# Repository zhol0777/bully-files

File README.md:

# bully-files

Bully is a keyboard designed by paaradiso keyboard design and zhol. It combines low typing angle, a plateless build, and modest but dignified design sensibilities. Its 13.5u width layout is designed for maximum compatibility with base kits that are missing minimum 40% keyboard support (“3-key”). Bully has a 22.4mm EKH, 4.0 degree angle, and bezels measuring 8mm and 3mm. 

The case files are provided in the [./case](./case/) directory, and alternative tops for HHKB layout (1.25u blocker) and WKL (1.25u blocker) are provided in their respective directories. 

This ran in a private run and public run by Coffee Break Keyboards in Q1 2023 and fulfilling Q2 2023.

## Required components
* Daughterboard
  * It is designed for [C3 Unified Daughterboard](https://github.com/Unified-Daughterboard/UDB-C-Legacy), but an updated daughterboard that takes JST-SH cables is provided [here](https://github.com/Unified-Daughterboard/UDB-C-JSH).
* Tadpoles
  * bully's PCB is fit into the case not with screws, but 8 injection molded rubber inserts named "tadpoles", from Geonworks.
  * [Files, courtesy Geon](https://geon.works/pages/tadpole-files)
* Screws
  * All screws are M2. Screws for daughterboard are 4mm, case screws are 6-ish mm.
* JST cable
  * As sold, bully took a 50mm 4-pin JST-SH cable. These cables are wired 1:1. I had no issues with Adafruit Qwiic JST SH cables sourced from Mouser. If you use an alternative connector on your PCB and daughterboard, you will need to ensure those cables are also 1:1.
* PCB
  * PCB edge cuts and plate files are provided in the [./misc](./misc/) directory. An electro-capacitive (commonly known as Topre, or NIZ Plum) compatible PCB is provided by sporkus [here](https://github.com/sporkus/capybully_keyboard). An alternative PCB compatible with Cherry MX and Alps switches is provided by sporkus [here](https://github.com/sporkus/bully2040_keyboard).
* Case feet.
  * bully uses [SKUF feet](https://github.com/Zambumon/SKUF).

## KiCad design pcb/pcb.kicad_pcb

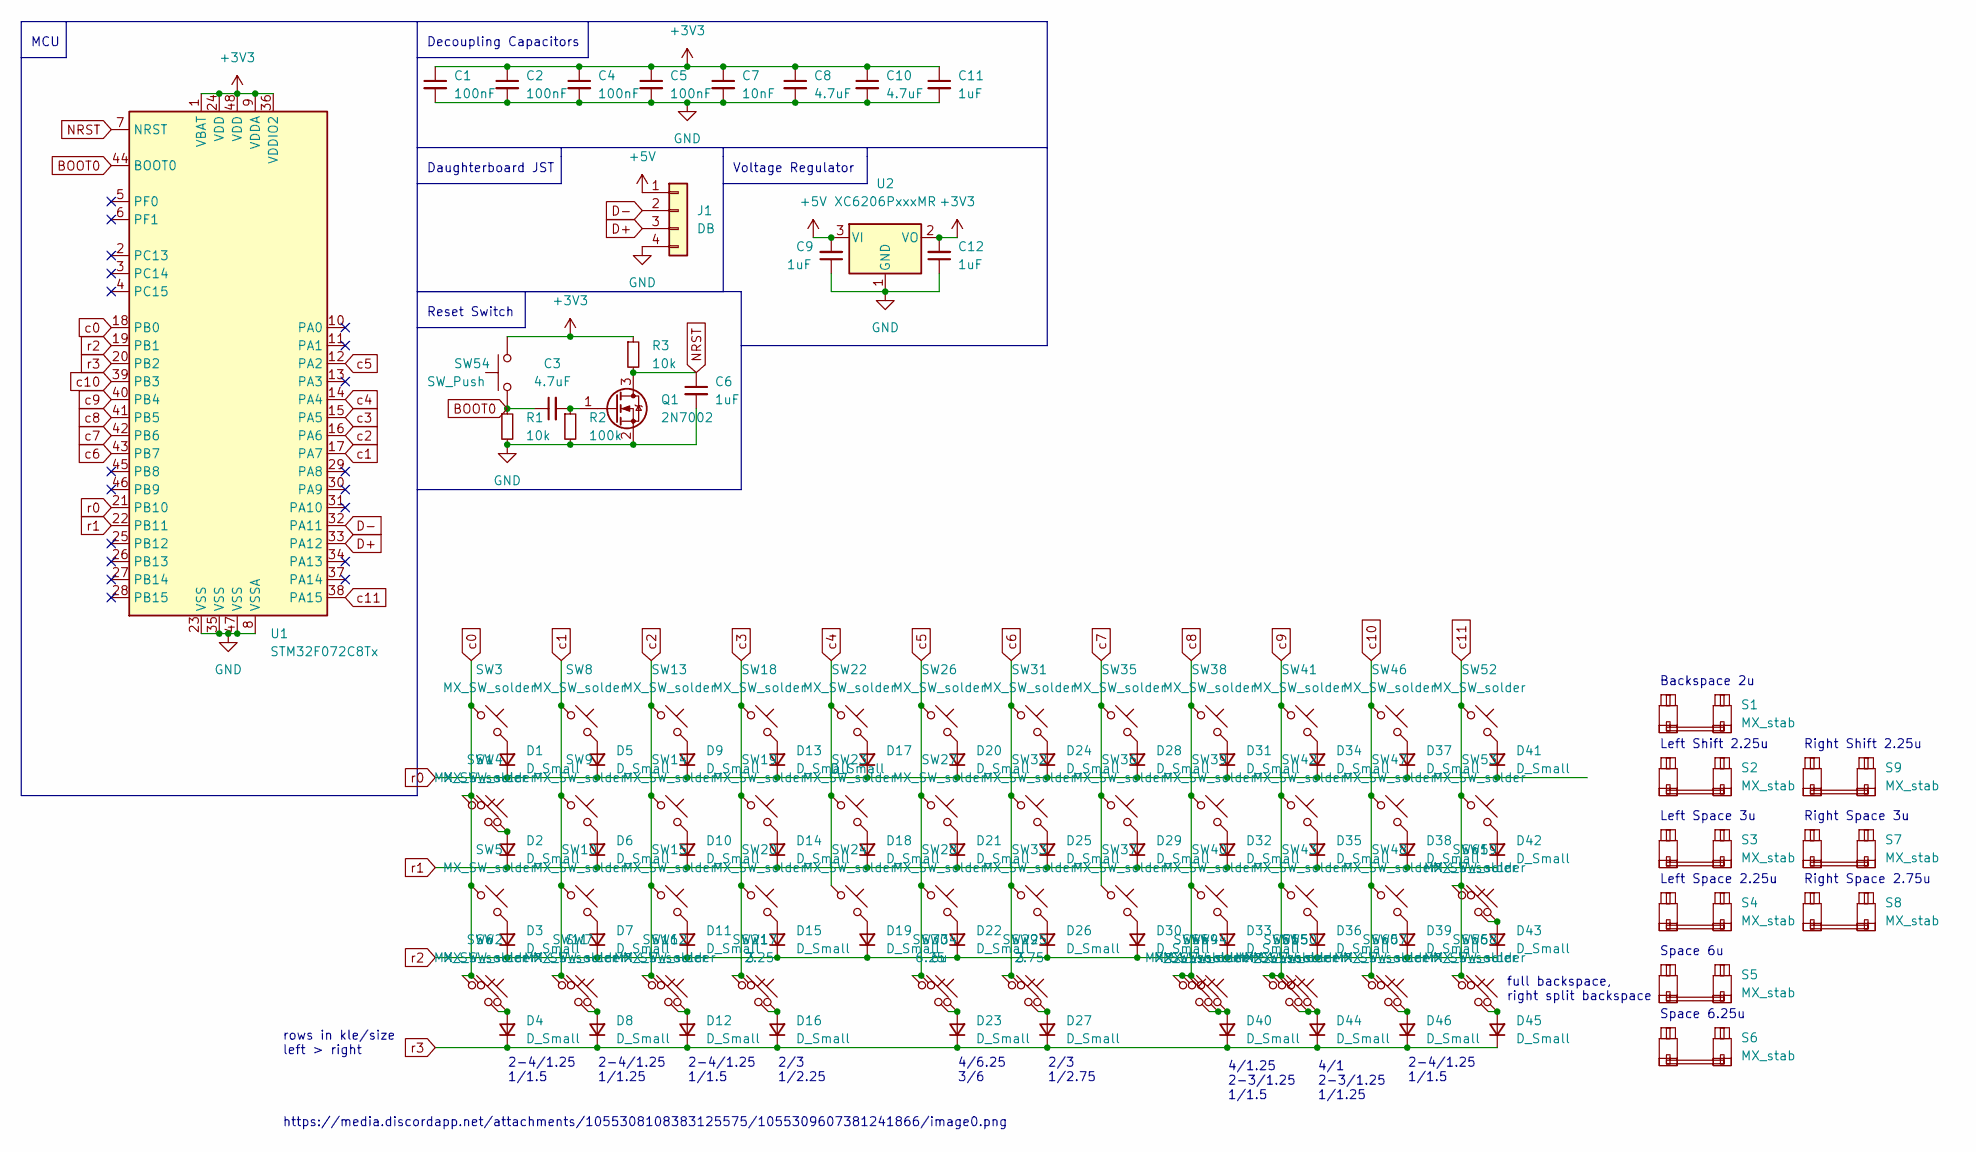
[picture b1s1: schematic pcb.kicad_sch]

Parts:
C1, C2, C4, C5: 100nF; C_0402_1005Metric
C3, C8, C10: 4.7uF; C_0402_1005Metric
C6, C9, C11, C12: 1uF; C_0402_1005Metric
C7: 10nF; C_0402_1005Metric
D1, D2, D3, D4, D5, D6, D7, D8, D9, D10, D11, D12, D13, D14, D15, D16, D17, D18, D19, D20, D21, D22, D23, D24, D25, D26, D27, D28, D29, D30, D31, D32, D33, D34, D35, D36, D37, D38, D39, D40, D41, D42, D43, D44, D45, D46: D_Small; D_SOD-123
J1: DB; JST_SH_SM04B-SRSS-TB_1x04-1MP_P1.00mm_Horizontal
Q1: 2N7002; SOT-23
R1, R3: 10k; R_0402_1005Metric
R2: 100k; R_0402_1005Metric
S1: MX_stab; STAB_MX_P_2u
S2, S4, S9: MX_stab; STAB_MX_P_2.25u
S3, S7: MX_stab; STAB_MX_P_3u
S5: MX_stab; STAB_MX_6u
S6: MX_stab; STAB_MX_6.25u
S8: MX_stab; STAB_MX_P_2.75u
SW1, SW53: MX_SW_solder; SW_MX_1.75u
SW2, SW3, SW12, SW44, SW57: MX_SW_solder; SW_MX_1.5u
SW4: MX_SW_solder; SW_MX_1.75u_stp
SW5, SW8, SW9, SW10, SW13, SW14, SW15, SW18, SW19, SW20, SW22, SW23, SW24, SW26, SW27, SW28, SW31, SW32, SW33, SW35, SW36, SW37, SW38, SW39, SW40, SW41, SW42, SW43, SW46, SW47, SW48, SW51, SW52, SW56, SW58, SW61: MX_SW_solder; SW_MX_1u
SW6, SW7, SW11, SW16, SW45, SW49, SW50, SW55, SW59, SW60: MX_SW_solder; SW_MX_1.25u
SW17: 2.25; SW_MX_1u
SW21, SW29: 3; SW_MX_1u
SW25: 2.75; SW_MX_1u
SW30: 6.25; SW_MX_1u
SW34: 6u; SW_MX_1u
SW54: SW_Push; SW_SPST_TL3342
U1: STM32F072C8Tx; LQFP-48_7x7mm_P0.5mm
U2: XC6206PxxxMR; SOT-23

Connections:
+3V3: C1.1, C2.1, C4.1, C5.1, C7.1, C8.1, C10.1, C11.1, C12.2, R3.1, SW54.2, U1.1 (VBAT), U1.9 (VDDA), U1.24 (VDD), U1.36 (VDDIO2), U1.48 (VDD), U2.2 (VO)
+5V: C9.2, J1.1, U2.3 (VI)
BOOT0: C3.1, R1.1, SW54.1, U1.44 (BOOT0)
D+: J1.3, U1.33 (PA12)
D-: J1.2, U1.32 (PA11)
GND: C1.2, C2.2, C4.2, C5.2, C6.2, C7.2, C8.2, C9.1, C10.2, C11.2, C12.1, J1.4, Q1.2 (S), R1.2, R2.2, U1.8 (VSSA), U1.23 (VSS), U1.35 (VSS), U1.47 (VSS), U2.1 (GND)
NRST: C6.1, Q1.3 (D), R3.2, U1.7 (NRST)
unnamed: D1.2 (A), SW3.2
unnamed: D2.2 (A), SW1.2, SW4.2
unnamed: D3.2 (A), SW5.2
unnamed: D4.2 (A), SW2.2, SW6.2
unnamed: D5.2 (A), SW8.2
unnamed: D6.2 (A), SW9.2
unnamed: D7.2 (A), SW10.2
unnamed: D8.2 (A), SW7.2, SW11.2
unnamed: D9.2 (A), SW13.2
unnamed: D10.2 (A), SW14.2
unnamed: D11.2 (A), SW15.2
unnamed: D12.2 (A), SW12.2, SW16.2
unnamed: D13.2 (A), SW18.2
unnamed: D14.2 (A), SW19.2
unnamed: D15.2 (A), SW20.2
unnamed: D16.2 (A), SW17.2, SW21.2
unnamed: D17.2 (A), SW22.2
unnamed: D18.2 (A), SW23.2
unnamed: D19.2 (A), SW24.2
unnamed: D20.2 (A), SW26.2
unnamed: D21.2 (A), SW27.2
unnamed: D22.2 (A), SW28.2
unnamed: D23.2 (A), SW30.2, SW34.2
unnamed: D24.2 (A), SW31.2
unnamed: D25.2 (A), SW32.2
unnamed: D26.2 (A), SW33.2
unnamed: D27.2 (A), SW25.2, SW29.2
unnamed: D28.2 (A), SW35.2
unnamed: D29.2 (A), SW36.2
unnamed: D30.2 (A), SW37.2
unnamed: D31.2 (A), SW38.2
unnamed: D32.2 (A), SW39.2
unnamed: D33.2 (A), SW40.2
unnamed: D34.2 (A), SW41.2
unnamed: D35.2 (A), SW42.2
unnamed: D36.2 (A), SW43.2
unnamed: D37.2 (A), SW46.2
unnamed: D38.2 (A), SW47.2
unnamed: D39.2 (A), SW48.2
unnamed: D40.2 (A), SW44.2, SW45.2, SW49.2
unnamed: D41.2 (A), SW52.2
unnamed: D42.2 (A), SW53.2
unnamed: D43.2 (A), SW59.2, SW61.2
unnamed: D44.2 (A), SW50.2, SW51.2, SW55.2
unnamed: D45.2 (A), SW56.2, SW58.2
unnamed: D46.2 (A), SW57.2, SW60.2
unnamed: C3.2, Q1.1 (G), R2.1
c0: SW1.1, SW2.1, SW3.1, SW4.1, SW5.1, SW6.1, U1.18 (PB0)
c1: SW7.1, SW8.1, SW9.1, SW10.1, SW11.1, U1.17 (PA7)
c2: SW12.1, SW13.1, SW14.1, SW15.1, SW16.1, U1.16 (PA6)
c3: SW17.1, SW18.1, SW19.1, SW20.1, SW21.1, U1.15 (PA5)
c4: SW22.1, SW23.1, SW24.1, U1.14 (PA4)
c5: SW26.1, SW27.1, SW28.1, SW30.1, SW34.1, U1.12 (PA2)
c6: SW25.1, SW29.1, SW31.1, SW32.1, SW33.1, U1.43 (PB7)
c7: SW35.1, SW36.1, SW37.1, U1.42 (PB6)
c8: SW38.1, SW39.1, SW40.1, SW44.1, SW45.1, SW49.1, U1.41 (PB5)
c9: SW41.1, SW42.1, SW43.1, SW50.1, SW51.1, SW55.1, U1.40 (PB4)
c10: SW46.1, SW47.1, SW48.1, SW57.1, SW60.1, U1.39 (PB3)
c11: SW52.1, SW53.1, SW56.1, SW58.1, SW59.1, SW61.1, U1.38 (PA15)
r0: D1.1 (K), D5.1 (K), D9.1 (K), D13.1 (K), D17.1 (K), D20.1 (K), D24.1 (K), D28.1 (K), D31.1 (K), D34.1 (K), D37.1 (K), D41.1 (K), U1.21 (PB10)
r1: D2.1 (K), D6.1 (K), D10.1 (K), D14.1 (K), D18.1 (K), D21.1 (K), D25.1 (K), D29.1 (K), D32.1 (K), D35.1 (K), D38.1 (K), D42.1 (K), U1.22 (PB11)
r2: D3.1 (K), D7.1 (K), D11.1 (K), D15.1 (K), D19.1 (K), D22.1 (K), D26.1 (K), D30.1 (K), D33.1 (K), D36.1 (K), D39.1 (K), D43.1 (K), U1.19 (PB1)
r3: D4.1 (K), D8.1 (K), D12.1 (K), D16.1 (K), D23.1 (K), D27.1 (K), D40.1 (K), D44.1 (K), D45.1 (K), D46.1 (K), U1.20 (PB2)

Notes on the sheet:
Backspace 2u
https://media.discordapp.net/attachments/1055308108383125575/1055309607381241866/image0.png
2-4/1.25 1/1.5
Daughterboard JST
Left Space 3u
4/1.25 2-3/1.25 1/1.5
full backspace, right split backspace
Voltage Regulator
2-4/1.25 1/1.25
Decoupling Capacitors
Right Shift 2.25u
2/3 1/2.75
rows in kle/size left > right
Right Space 3u
Space 6.25u
2/3 1/2.25
Reset Switch
4/1 2-3/1.25 1/1.25
Space 6u
Left Shift 2.25u
4/6.25 3/6
Right Space 2.75u
MCU
Left Space 2.25u

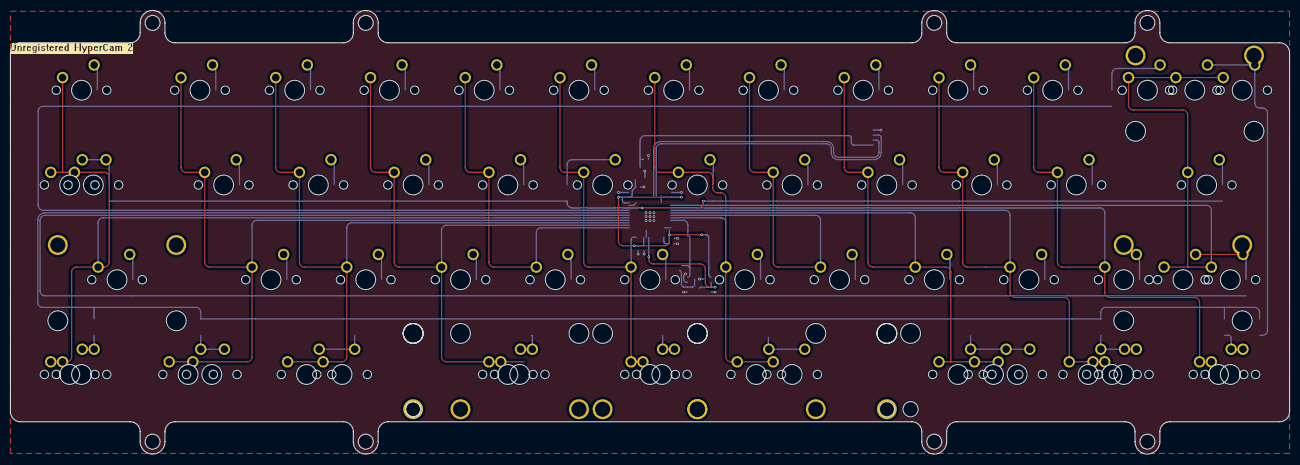
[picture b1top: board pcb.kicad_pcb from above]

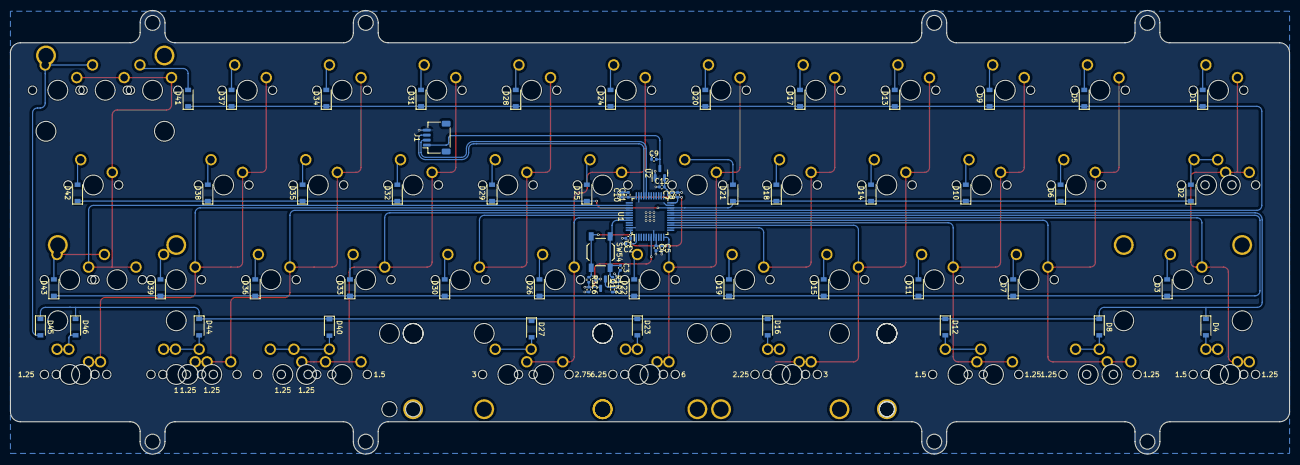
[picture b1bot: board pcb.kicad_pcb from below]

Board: 2 copper layers, 257.2 x 89.2 mm, 135 parts (66 on the bottom side), 70 nets.

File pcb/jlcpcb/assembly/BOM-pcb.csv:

Comment,Designator,Footprint,LCSC
10nF,C7,C_0402_1005Metric,C15195
4.7uF,"C10,C3,C8",C_0402_1005Metric,C23733
100k,R2,R_0402_1005Metric,C25741
10k,"R1,R3",R_0402_1005Metric,C25744
DB,J1,JST_SH_SM04B-SRSS-TB_1x04-1MP_P1.00mm_Horizontal,C2845363
100nF,"C1,C2,C4,C5",C_0402_1005Metric,C307331
SW_Push,SW54,SW_SPST_TL3342,C318884
1uF,"C11,C12,C6,C9",C_0402_1005Metric,C52923
XC6206PxxxMR,U2,SOT-23,C5446
D_Small,"D1,D10,D11,D12,D13,D14,D15,D16,D17,D18,D19,D2,D20,D21,D22,D23,D24,D25,D26,D27,D28,D29,D3,D30,D31,D32,D33,D34,D35,D36,D37,D38,D39,D4,D40,D41,D42,D43,D44,D45,D46,D5,D6,D7,D8,D9",D_SOD-123,C81598
2N7002,Q1,SOT-23,C8545
STM32F072C8Tx,U1,LQFP-48_7x7mm_P0.5mm,C915660
MX_SW_solder,SW10,SW_MX_1u,
MX_SW_solder,SW48,SW_MX_1u,
MX_SW_solder,SW49,SW_MX_1.25u,
MX_SW_solder,SW41,SW_MX_1u,
MX_SW_solder,SW25,SW_MX_1u,
MX_SW_solder,SW1,SW_MX_1.75u,
MX_SW_solder,SW57,SW_MX_1.5u,
MX_SW_solder,SW8,SW_MX_1u,
MX_SW_solder,SW60,SW_MX_1.25u,
MX_SW_solder,SW55,SW_MX_1.25u,
MX_SW_solder,SW59,SW_MX_1.25u,
MX_SW_solder,SW15,SW_MX_1u,
MX_SW_solder,SW36,SW_MX_1u,
MX_SW_solder,SW33,SW_MX_1u,
MX_SW_solder,SW6,SW_MX_1.25u,
MX_SW_solder,SW30,SW_MX_1u,
MX_SW_solder,SW31,SW_MX_1u,
MX_SW_solder,SW21,SW_MX_1u,
MX_SW_solder,SW7,SW_MX_1.25u,
MX_stab,S5,STAB_MX_6u,
MX_SW_solder,SW13,SW_MX_1u,
MX_SW_solder,SW5,SW_MX_1u,
MX_SW_solder,SW16,SW_MX_1.25u,
MX_SW_solder,SW24,SW_MX_1u,
MX_SW_solder,SW23,SW_MX_1u,
MX_SW_solder,SW46,SW_MX_1u,
MX_stab,S2,STAB_MX_P_2.25u,
MX_SW_solder,SW26,SW_MX_1u,
MX_stab,S8,STAB_MX_P_2.75u,
MX_SW_solder,SW29,SW_MX_1u,
MX_SW_solder,SW43,SW_MX_1u,
MX_SW_solder,SW37,SW_MX_1u,
MX_SW_solder,SW50,SW_MX_1.25u,
MX_SW_solder,SW2,SW_MX_1.5u,
MX_SW_solder,SW56,SW_MX_1u,
MX_SW_solder,SW47,SW_MX_1u,
MX_SW_solder,SW35,SW_MX_1u,
MX_stab,S4,STAB_MX_P_2.25u,
MX_SW_solder,SW42,SW_MX_1u,
MX_SW_solder,SW32,SW_MX_1u,
MX_SW_solder,SW19,SW_MX_1u,
MX_SW_solder,SW4,SW_MX_1.75u_stp,
MX_SW_solder,SW40,SW_MX_1u,
MX_SW_solder,SW9,SW_MX_1u,
MX_SW_solder,SW52,SW_MX_1u,
MX_stab,S7,STAB_MX_P_3u,
MX_SW_solder,SW12,SW_MX_1.5u,
MX_stab,S6,STAB_MX_6.25u,
MX_SW_solder,SW51,SW_MX_1u,
MX_SW_solder,SW34,SW_MX_1u,
MX_SW_solder,SW39,SW_MX_1u,
MX_SW_solder,SW53,SW_MX_1.75u,
MX_SW_solder,SW27,SW_MX_1u,
MX_stab,S1,STAB_MX_P_2u,
MX_SW_solder,SW22,SW_MX_1u,
MX_SW_solder,SW20,SW_MX_1u,
MX_SW_solder,SW45,SW_MX_1.25u,
MX_SW_solder,SW38,SW_MX_1u,
MX_SW_solder,SW44,SW_MX_1.5u,
MX_SW_solder,SW28,SW_MX_1u,
MX_SW_solder,SW17,SW_MX_1u,
MX_SW_solder,SW18,SW_MX_1u,
MX_SW_solder,SW14,SW_MX_1u,
MX_SW_solder,SW3,SW_MX_1.5u,
MX_stab,S3,STAB_MX_P_3u,
MX_SW_solder,SW11,SW_MX_1.25u,
MX_SW_solder,SW58,SW_MX_1u,
MX_SW_solder,SW61,SW_MX_1u,
MX_stab,S9,STAB_MX_P_2.25u,

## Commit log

2023-05-12 init
2023-05-12 add license
2023-05-18 Adding 1.25 WKL Top
    Who would use this?
2023-05-18 Rename Top - WKL.STEP to wkl_6u.STEP
2023-06-04 add warning about libusb_timeout_error
2023-12-18 add case files
2023-12-18 README
2023-12-18 forgot feet
